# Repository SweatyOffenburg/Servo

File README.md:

# Servo
Publication of Sweaty's servo

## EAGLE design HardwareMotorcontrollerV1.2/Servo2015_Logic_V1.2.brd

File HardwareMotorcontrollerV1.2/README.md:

# Servo
Publication of Sweaty's servo Hardware describede 12th Workshop on Humanoid Soccer Robots IEEE RAS International Conference on Humanoid Robots — November 15-17, 2017, Birmingham (UK)
  /

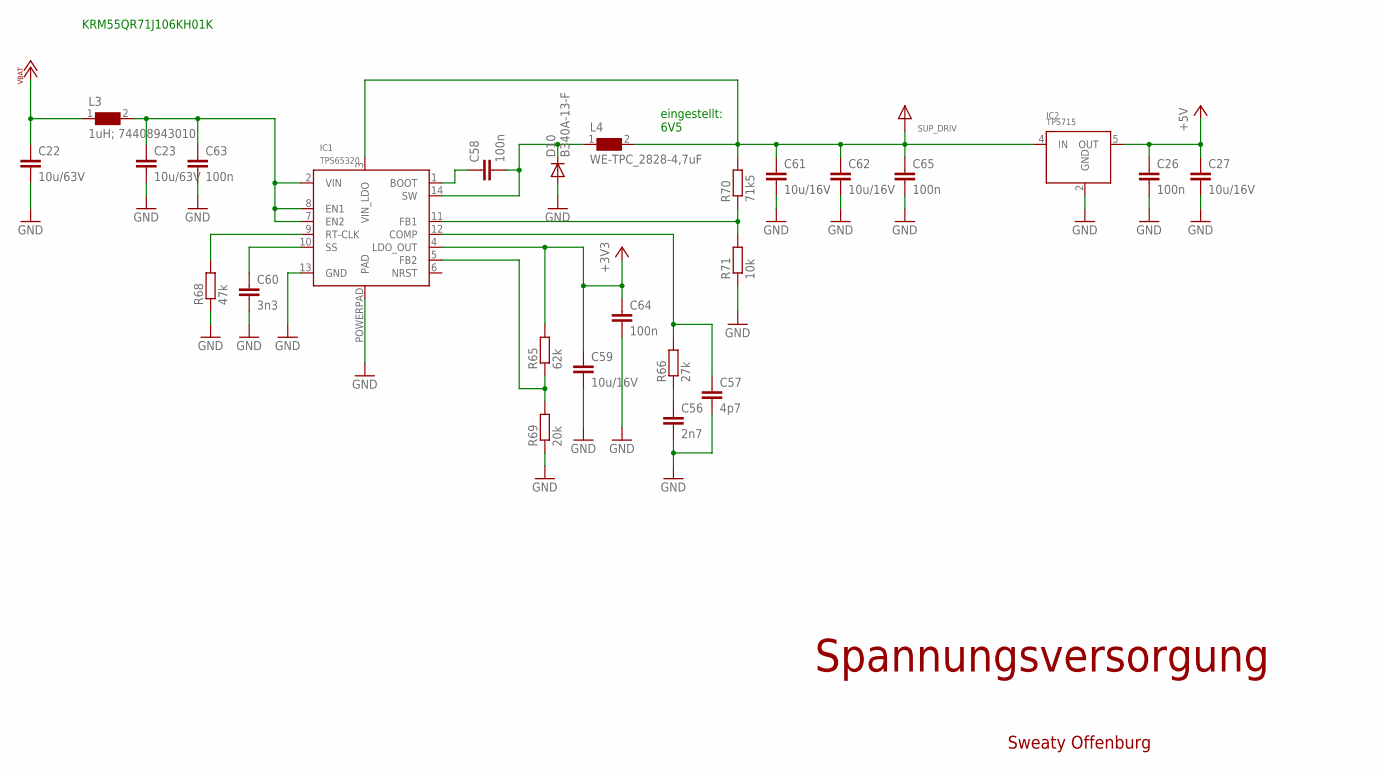
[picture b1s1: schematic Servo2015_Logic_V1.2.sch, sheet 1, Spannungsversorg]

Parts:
C22, C23: 10u/63V; C2220K
C26, C58, C63, C64, C65: 100n; C0603
C27, C59, C61, C62: 10u/16V; C0805
C56: 2n7; C0603
C57: 4p7; C0603
C60: 3n3; C0603
D10: B340A-13-F; SMA
IC1: TPS65320; R.PDSO.G14_PWP
IC2: TPS715; SC-70_DCK_R_PDSO_G5
L3: 1uH; 74408943010; WE-SPC_48XX
L4: WE-TPC_2828-4,7uF; WE-TPC_2828
R65: 62k; R0603
R66: 27k; R0603
R68: 47k; R0603
R69: 20k; R0603
R70: 71k5; R0603
R71: 10k; R0603

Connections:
+3V3: C59.1, C64.1, IC1.4 (LDO_OUT), R65.2; also elsewhere on the board
+5V: C26.1, C27.1, IC2.5 (OUT); also elsewhere on the board
GND: C22.2, C23.2, C26.2, C27.2, C56.2, C57.2, C59.2, C60.2, C61.2, C62.2, C63.2, C64.2, C65.2, D10.A, IC1.13 (GND), IC1.POWERPAD (PAD), IC2.2 (GND), R68.1, R69.1, R71.1; also elsewhere on the board
unnamed: C57.1, IC1.12 (COMP), R66.2
unnamed: C56.1, R66.1
unnamed: IC1.5 (FB2), R65.1, R69.2
unnamed: C58.2, D10.C, IC1.14 (SW), L4.1
unnamed: IC1.11 (FB1), R70.1, R71.2
unnamed: C60.1, IC1.10 (SS)
unnamed: IC1.9 (RT-CLK), R68.2
unnamed: C23.1, C63.1, IC1.2 (VIN), IC1.7 (EN2), IC1.8 (EN1), L3.2
unnamed: C58.1, IC1.1 (BOOT)
SUP_DRIV: C61.1, C62.1, C65.1, IC1.3 (VIN_LDO), IC2.4 (IN), L4.2, R70.2; also elsewhere on the board
VBAT+: C22.1, L3.1; also elsewhere on the board

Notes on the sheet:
Spannungsversorgung
eingestellt: 6V5
KRM55QR71J106KH01K
Sweaty Offenburg

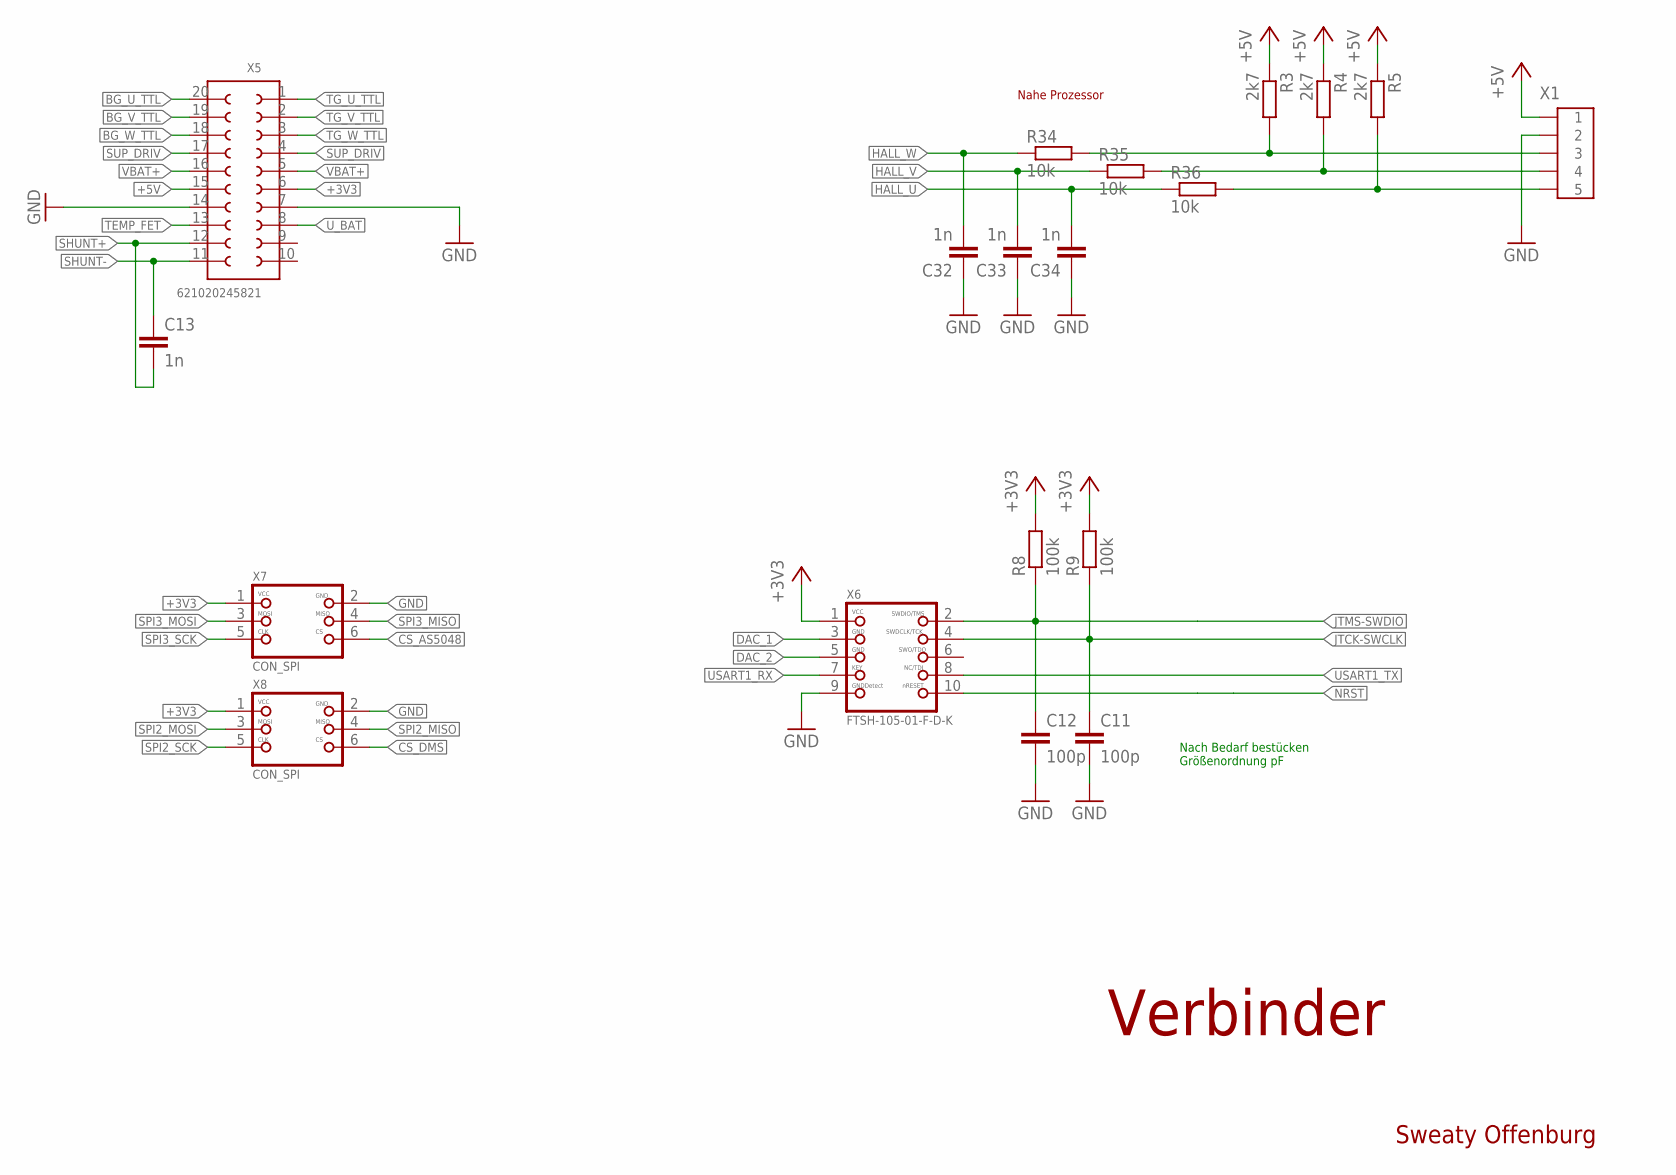
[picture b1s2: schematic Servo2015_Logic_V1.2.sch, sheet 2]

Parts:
C11, C12: 100p; C0603
C13, C32, C33, C34: 1n; C0603
R3, R4, R5: 2k7; R0603
R8, R9: 100k; R0603
R34, R35, R36: 10k; R0603
X1: HALL-5POL-SERVOBOARD; MOLEX-SPOX-5POL-VERT
X5: 621020245821
X6: FTSH-105-01-F-D-K; 2X05_1.27MM_SMT
X7, X8: CON_SPI; 2X03_1.27MM_SMT

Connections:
+3V3: R8.2, R9.2, X5.6, X6.1, X7.1, X8.1; also elsewhere on the board
+5V: R3.1, R4.1, R5.1, X1.1, X5.15; also elsewhere on the board
BG_U_TTL: X5.20; also elsewhere on the board
BG_V_TTL: X5.19; also elsewhere on the board
BG_W_TTL: X5.18; also elsewhere on the board
CS_AS5048: X7.6; also elsewhere on the board
CS_DMS: X8.6; also elsewhere on the board
DAC_1: X6.3; also elsewhere on the board
DAC_2: X6.5; also elsewhere on the board
GND: C11.2, C12.2, C32.1, C33.1, C34.1, X1.2, X5.7, X5.14, X6.9, X7.2, X8.2; also elsewhere on the board
HALL_U: C34.2, R36.1; also elsewhere on the board
HALL_V: C33.2, R35.1; also elsewhere on the board
HALL_W: C32.2, R34.1; also elsewhere on the board
JTCK-SWCLK: C11.1, R9.1, X6.4; also elsewhere on the board
JTMS-SWDIO: C12.1, R8.1, X6.2; also elsewhere on the board
unnamed: R3.2, R34.2, X1.3
unnamed: R4.2, R35.2, X1.4
unnamed: R5.2, R36.2, X1.5
NRST: X6.10; also elsewhere on the board
SHUNT+: C13.2, X5.12; also elsewhere on the board
SHUNT-: C13.1, X5.11; also elsewhere on the board
SPI2_MISO: X8.4; also elsewhere on the board
SPI2_MOSI: X8.3; also elsewhere on the board
SPI2_SCK: X8.5; also elsewhere on the board
SPI3_MISO: X7.4; also elsewhere on the board
SPI3_MOSI: X7.3; also elsewhere on the board
SPI3_SCK: X7.5; also elsewhere on the board
SUP_DRIV: X5.4, X5.17; also elsewhere on the board
TEMP_FET: X5.13; also elsewhere on the board
TG_U_TTL: X5.1; also elsewhere on the board
TG_V_TTL: X5.2; also elsewhere on the board
TG_W_TTL: X5.3; also elsewhere on the board
USART1_RX: X6.7; also elsewhere on the board
USART1_TX: X6.8; also elsewhere on the board
U_BAT: X5.8; also elsewhere on the board
VBAT+: X5.5, X5.16; also elsewhere on the board

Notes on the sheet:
Verbinder
Nahe Prozessor
Nach Bedarf bestücken Größenordnung pF
Sweaty Offenburg

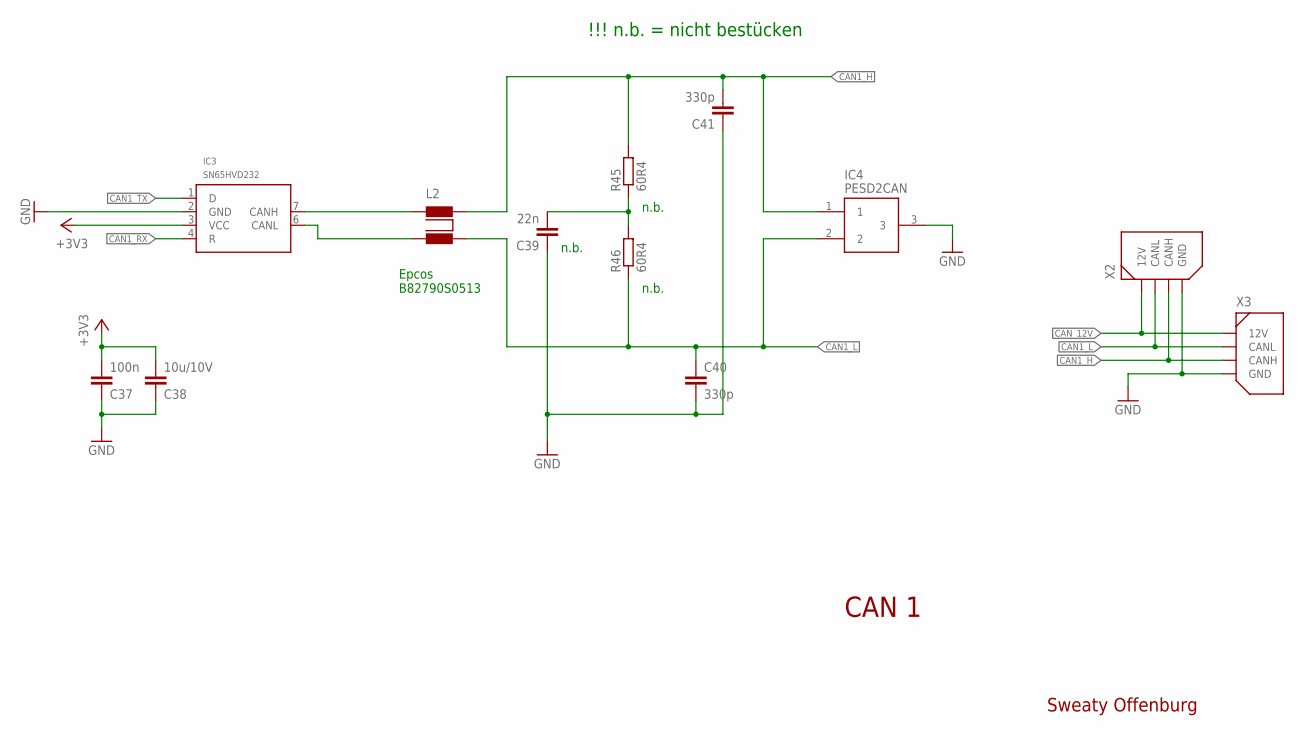
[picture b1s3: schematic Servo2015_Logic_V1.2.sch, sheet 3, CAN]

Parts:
C37: 100n; C0603
C38: 10u/10V; C0603
C39: 22n; C0603
C40, C41: 330p; C0603
IC3: SN65HVD232; SO-8
IC4: PESD2CAN; SOT-23(TO263AB)
L2: B82790S0513; B82790C0/S0
R45, R46: 60R4; R0805
X2, X3: CAN-4POL; MOLEX-SPOX-4PO

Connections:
+3V3: C37.2, C38.2, IC3.3 (VCC); also elsewhere on the board
CAN1_H: C41.2, IC4.1, L2.2, R45.2, X2.P$3 (CANH), X3.P$3 (CANH)
CAN1_L: C40.1, IC4.2, L2.3, R46.1, X2.P$2 (CANL), X3.P$2 (CANL)
CAN1_RX: IC3.4 (R); also elsewhere on the board
CAN1_TX: IC3.1 (D); also elsewhere on the board
CAN_12V: X2.P$1 (12V), X3.P$1 (12V)
GND: C37.1, C38.1, C39.1, C40.2, C41.1, IC3.2 (GND), IC4.3, X2.P$4 (GND), X3.P$4 (GND); also elsewhere on the board
unnamed: C39.2, R45.1, R46.2
unnamed: IC3.7 (CANH), L2.1
unnamed: IC3.6 (CANL), L2.4

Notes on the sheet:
Epcos B82790S0513
CAN 1
n.b.
!!! n.b. = nicht bestücken
Sweaty Offenburg

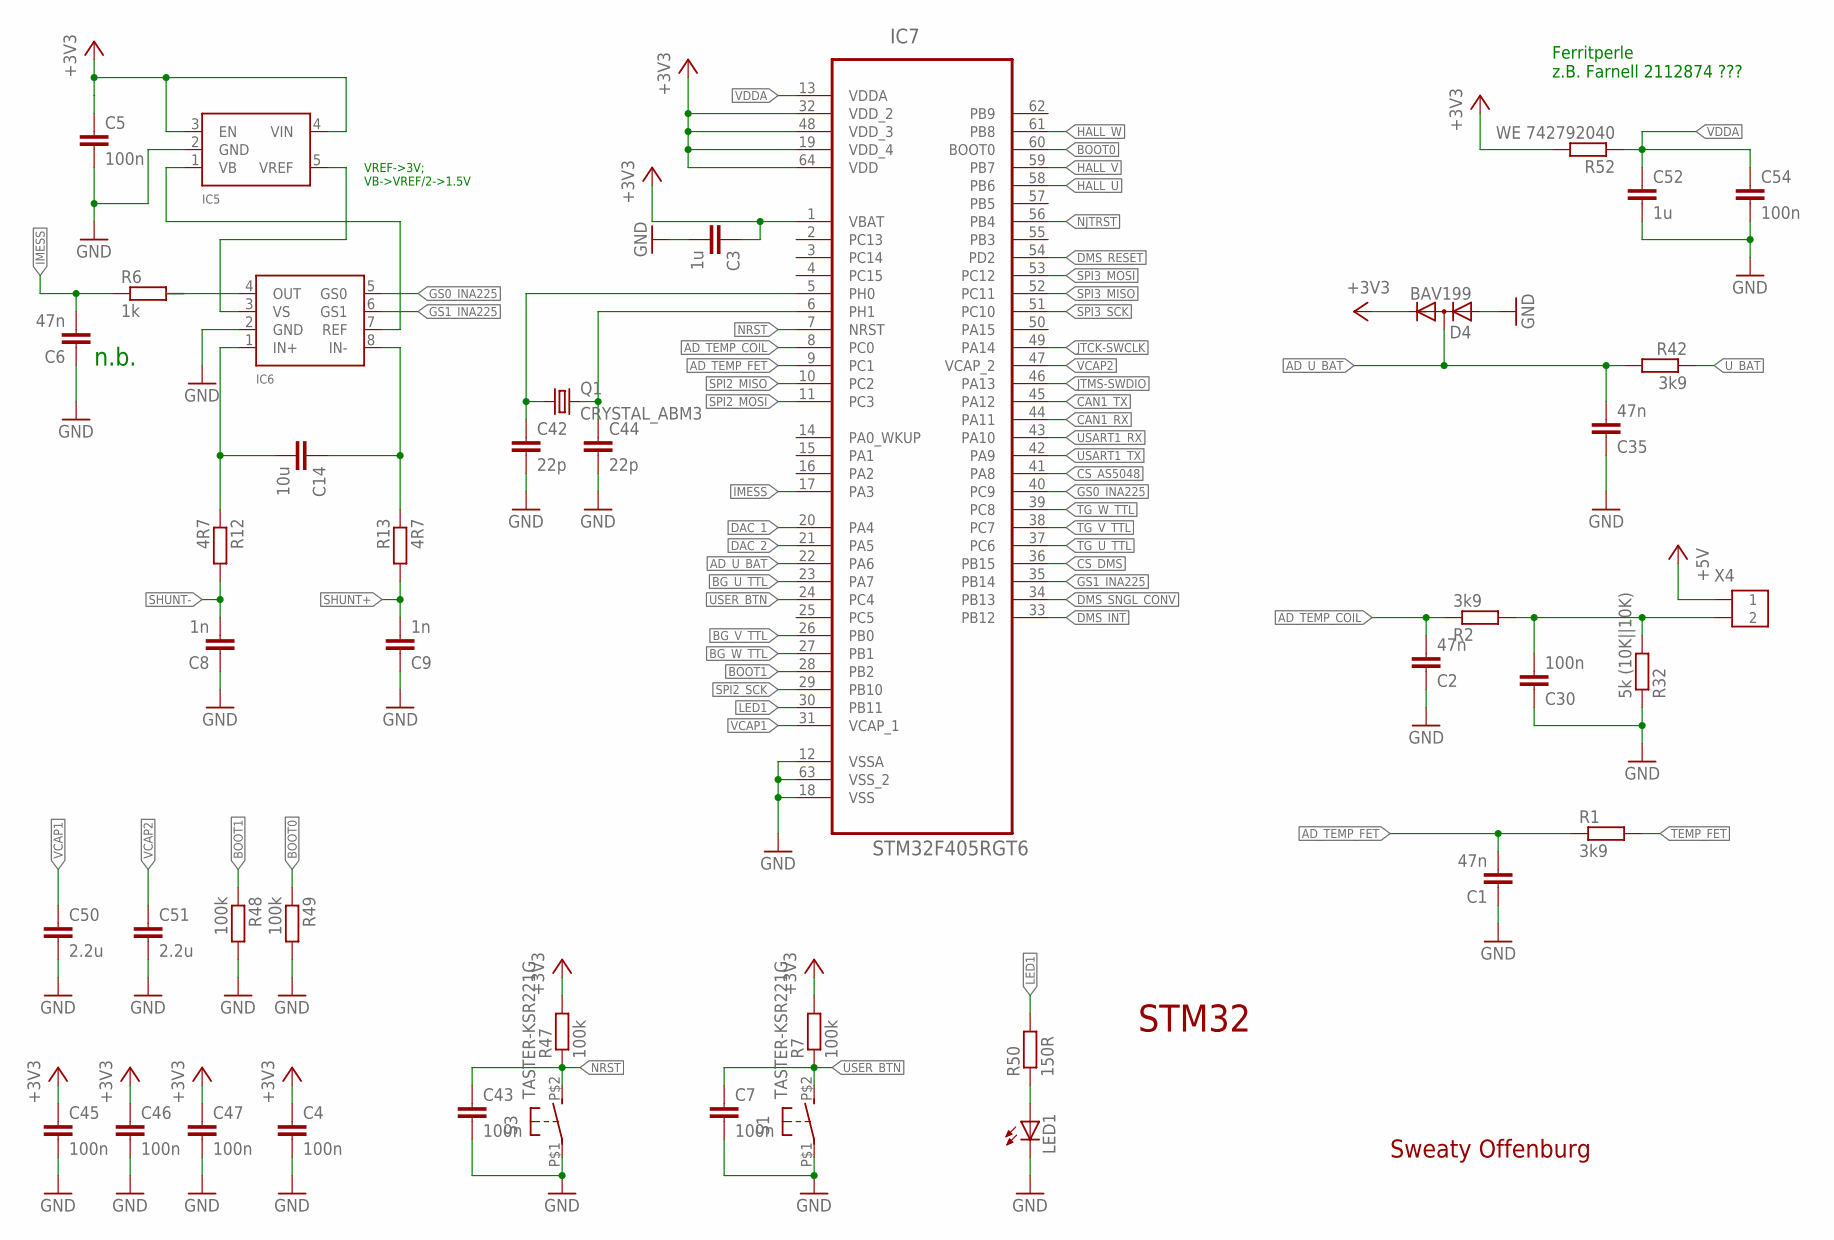
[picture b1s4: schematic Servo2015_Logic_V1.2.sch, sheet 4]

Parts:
C1, C2, C6, C35: 47n; C0603
C3, C52: 1u; C0603
C4, C5, C7, C30, C43, C45, C46, C47, C54: 100n; C0603
C8, C9: 1n; C0603
C14: 10u; C0603
C42, C44: 22p; C0603
C50, C51: 2.2u; C0603
D4: BAV199; SOT23
IC5: REF2030; R-PDSO-G5
IC6: INA225; S-PDSO-G8
IC7: STM32F405RGT6; QFP50P1200X1200X160-64N
LED1: LEDCHIPLED_0805; CHIPLED_0805
Q1: CRYSTAL_ABM3; CRYSTAL-5X3.2
R1, R2, R42: 3k9; R0603
R6: 1k; R0603
R7, R47, R48, R49: 100k; R0603
R12, R13: 4R7; R0603
R32: 5k (10K||10K); R0603
R50: 150R; R0603
R52: WE 742792040; R0805
S1, S3: TASTER-KSR221G; KSR-TASTER
X4: KRAFTSENSOR-2POL; MOLEX-SPOX-2POL

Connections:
+3V3: C3.1, C4.1, C5.1, C45.1, C46.1, C47.1, D4.2 (C), IC5.3 (EN), IC5.4 (VIN), IC7.1 (VBAT), IC7.19 (VDD_4), IC7.32 (VDD_2), IC7.48 (VDD_3), IC7.64 (VDD), R7.2, R47.2, R52.2; also elsewhere on the board
+5V: X4.P$1 (1); also elsewhere on the board
AD_TEMP_COIL: C2.2, IC7.8 (PC0), R2.1
AD_TEMP_FET: C1.2, IC7.9 (PC1), R1.1
AD_U_BAT: C35.2, D4.3 (AC), IC7.22 (PA6), R42.2
BG_U_TTL: IC7.23 (PA7); also elsewhere on the board
BG_V_TTL: IC7.26 (PB0); also elsewhere on the board
BG_W_TTL: IC7.27 (PB1); also elsewhere on the board
BOOT0: IC7.60 (BOOT0), R49.1
BOOT1: IC7.28 (PB2), R48.1
CAN1_RX: IC7.44 (PA11); also elsewhere on the board
CAN1_TX: IC7.45 (PA12); also elsewhere on the board
CS_AS5048: IC7.41 (PA8); also elsewhere on the board
CS_DMS: IC7.36 (PB15); also elsewhere on the board
DAC_1: IC7.20 (PA4); also elsewhere on the board
DAC_2: IC7.21 (PA5); also elsewhere on the board
DMS_INT: IC7.33 (PB12)
DMS_RESET: IC7.54 (PD2)
DMS_SNGL_CONV: IC7.34 (PB13)
GND: C1.1, C2.1, C3.2, C4.2, C5.2, C6.1, C7.2, C8.1, C9.1, C30.1, C35.1, C42.2, C43.2, C44.2, C45.2, C46.2, C47.2, C50.2, C51.2, C52.2, C54.2, D4.1 (A), IC5.2 (GND), IC6.2 (GND), IC7.12 (VSSA), IC7.18 (VSS), IC7.63 (VSS_2), LED1.C, R32.1, R48.2, R49.2, S1.P$1, S3.P$1; also elsewhere on the board
GS0_INA225: IC6.5 (GS0), IC7.40 (PC9)
GS1_INA225: IC6.6 (GS1), IC7.35 (PB14)
HALL_U: IC7.58 (PB6); also elsewhere on the board
HALL_V: IC7.59 (PB7); also elsewhere on the board
HALL_W: IC7.61 (PB8); also elsewhere on the board
IC6: C14.2, IC6.1 (IN+), R12.1
IMESS: C6.2, IC7.17 (PA3), R6.1
JTCK-SWCLK: IC7.49 (PA14); also elsewhere on the board
JTMS-SWDIO: IC7.46 (PA13); also elsewhere on the board
LED1: IC7.30 (PB11), R50.2
unnamed: C14.1, IC6.8 (IN-), R13.1
unnamed: LED1.A, R50.1
unnamed: IC6.4 (OUT), R6.2
unnamed: IC5.5 (VREF), IC6.3 (VS)
unnamed: IC5.1 (VB), IC6.7 (REF)
unnamed: C44.1, IC7.6 (PH1), Q1.P$2 (2)
unnamed: C42.1, IC7.5 (PH0), Q1.P$1 (1)
NJTRST: IC7.56 (PB4)
NRST: C43.1, IC7.7 (NRST), R47.1, S3.P$2 (S); also elsewhere on the board
SHUNT+: C9.2, R13.2; also elsewhere on the board
SHUNT-: C8.2, R12.2; also elsewhere on the board
SPI2_MISO: IC7.10 (PC2); also elsewhere on the board
SPI2_MOSI: IC7.11 (PC3); also elsewhere on the board
SPI2_SCK: IC7.29 (PB10); also elsewhere on the board
SPI3_MISO: IC7.52 (PC11); also elsewhere on the board
SPI3_MOSI: IC7.53 (PC12); also elsewhere on the board
SPI3_SCK: IC7.51 (PC10); also elsewhere on the board
TEMP_COIL: C30.2, R2.2, R32.2, X4.P$2 (2)
TEMP_FET: R1.2; also elsewhere on the board
TG_U_TTL: IC7.37 (PC6); also elsewhere on the board
TG_V_TTL: IC7.38 (PC7); also elsewhere on the board
TG_W_TTL: IC7.39 (PC8); also elsewhere on the board
USART1_RX: IC7.43 (PA10); also elsewhere on the board
USART1_TX: IC7.42 (PA9); also elsewhere on the board
USER_BTN: C7.1, IC7.24 (PC4), R7.1, S1.P$2 (S)
U_BAT: R42.1; also elsewhere on the board
VCAP1: C50.1, IC7.31 (VCAP_1)
VCAP2: C51.1, IC7.47 (VCAP_2)
VDDA: C52.1, C54.1, IC7.13 (VDDA), R52.1

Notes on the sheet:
Ferritperle z.B. Farnell 2112874 ???
STM32
VREF->3V; VB->VREF/2->1.5V
n.b.
Sweaty Offenburg

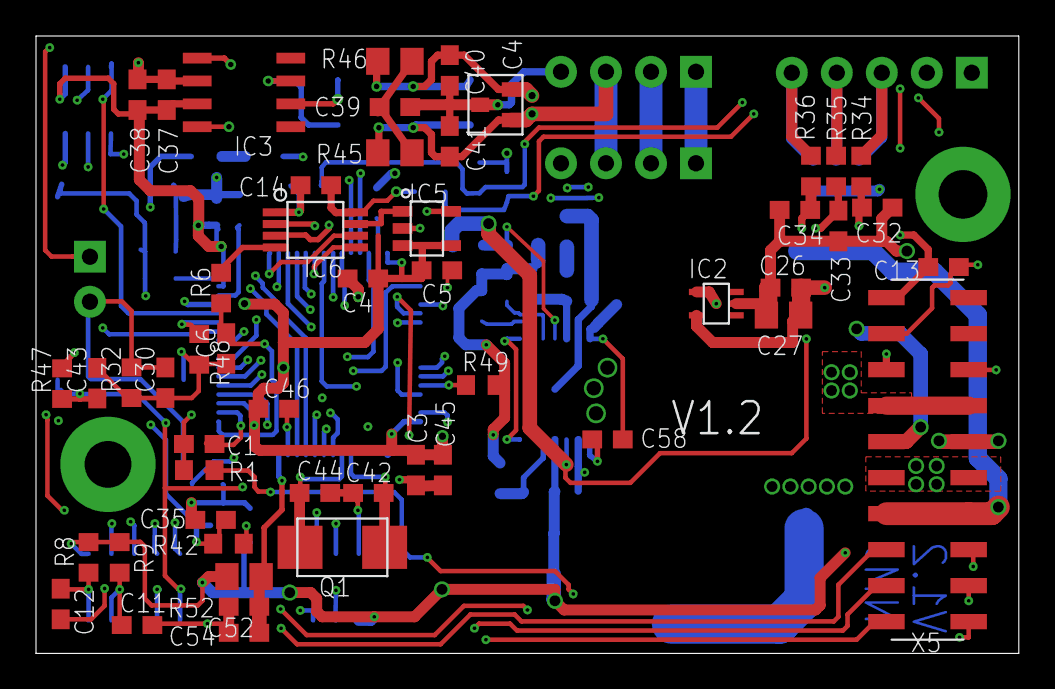
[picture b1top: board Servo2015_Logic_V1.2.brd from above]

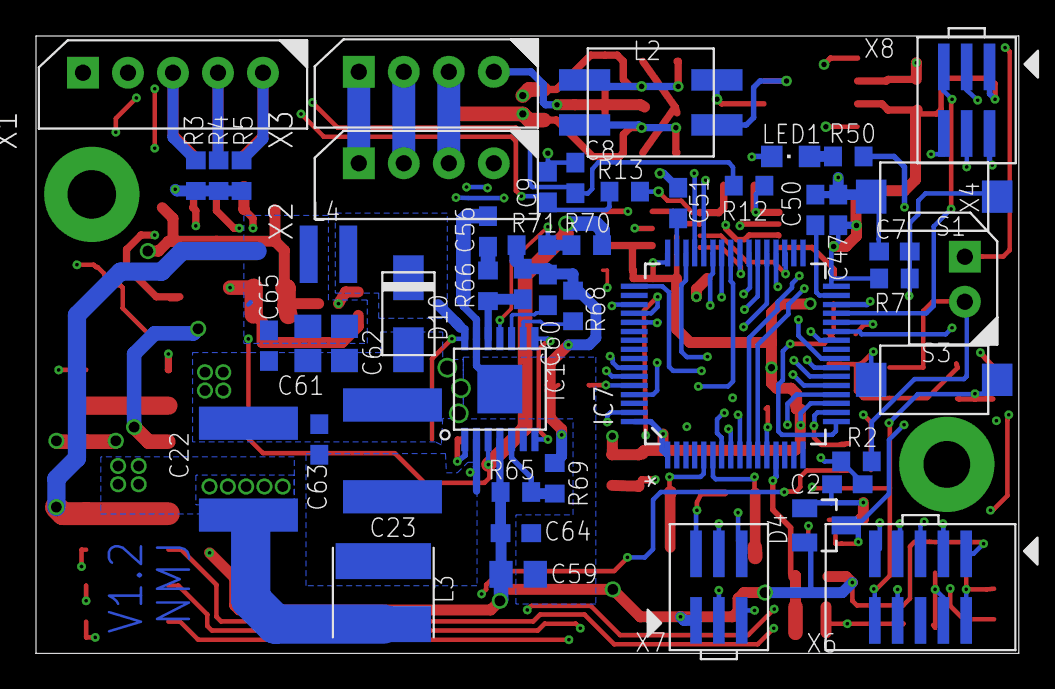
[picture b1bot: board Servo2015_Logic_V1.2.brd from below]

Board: 4 copper layers, 54.6 x 34.3 mm, 101 parts (49 on the bottom side), 75 nets.

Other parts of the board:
U$1: A4L-LOC

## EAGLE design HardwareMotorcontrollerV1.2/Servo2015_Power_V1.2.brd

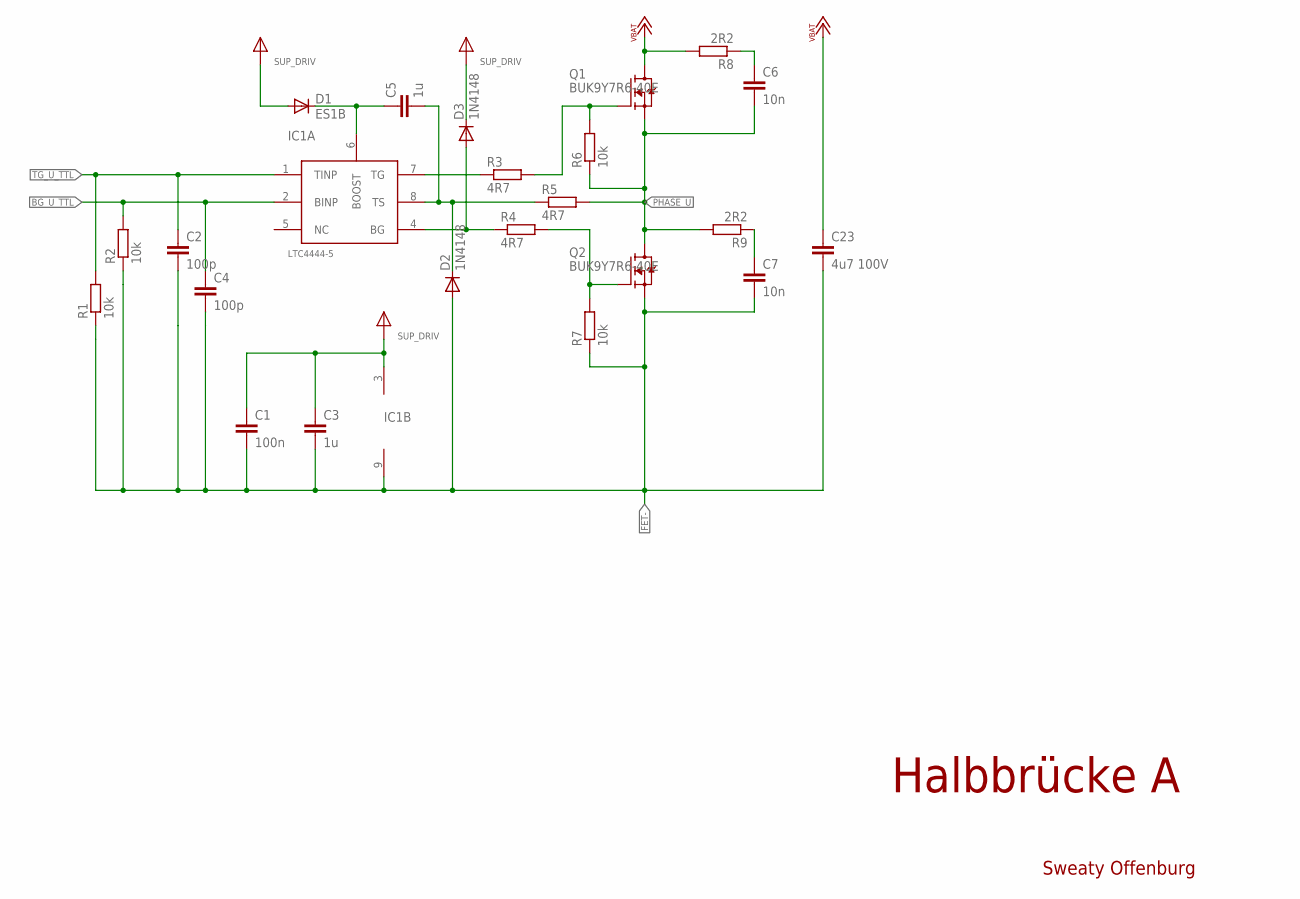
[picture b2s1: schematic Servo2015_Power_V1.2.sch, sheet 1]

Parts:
C1: 100n; C0603
C2, C4: 100p; C0603
C3, C5: 1u; C0603
C6, C7: 10n; C1210
C23: 4u7 100V; C2220K
D1: ES1B; DO214AC
D2, D3: 1N4148; SOD123
IC1: LTC4444-5; MS8E
Q1, Q2: BUK9Y7R6-40E; LFPAK56
R1, R2, R6, R7: 10k; R0603
R3, R4, R5: 4R7; R0805
R8, R9: 2R2; R1206

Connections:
BGR_A: Q2.4 (G), R4.2, R7.2
BG_U_TTL: C4.1, IC1.2 (BINP), R2.2; also elsewhere on the board
FET-: C1.2, C2.2, C3.2, C4.2, C7.2, C23.2, D2.A, IC1.9 (GND), Q2.1 (S), Q2.2 (S), Q2.3 (S), R1.1, R2.1, R7.1; also elsewhere on the board
unnamed: IC1.7 (TG), R3.1
unnamed: C5.2, D2.C, IC1.8 (TS), R5.1
unnamed: D3.A, IC1.4 (BG), R4.1
unnamed: C5.1, D1.C, IC1.6 (BOOST)
unnamed: C6.1, R8.1
unnamed: C7.1, R9.1
PHASE_U: C6.2, Q1.1 (S), Q1.2 (S), Q1.3 (S), Q2.5-8 (D), R5.2, R6.1, R9.2; also elsewhere on the board
SUP_DRIV: C1.1, C3.1, D1.A, D3.C, IC1.3 (VCC); also elsewhere on the board
TGR_A: Q1.4 (G), R3.2, R6.2
TG_U_TTL: C2.1, IC1.1 (TINP), R1.2; also elsewhere on the board
VBAT+: C23.1, Q1.5-8 (D), R8.2; also elsewhere on the board

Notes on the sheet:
Halbbrücke A
Sweaty Offenburg

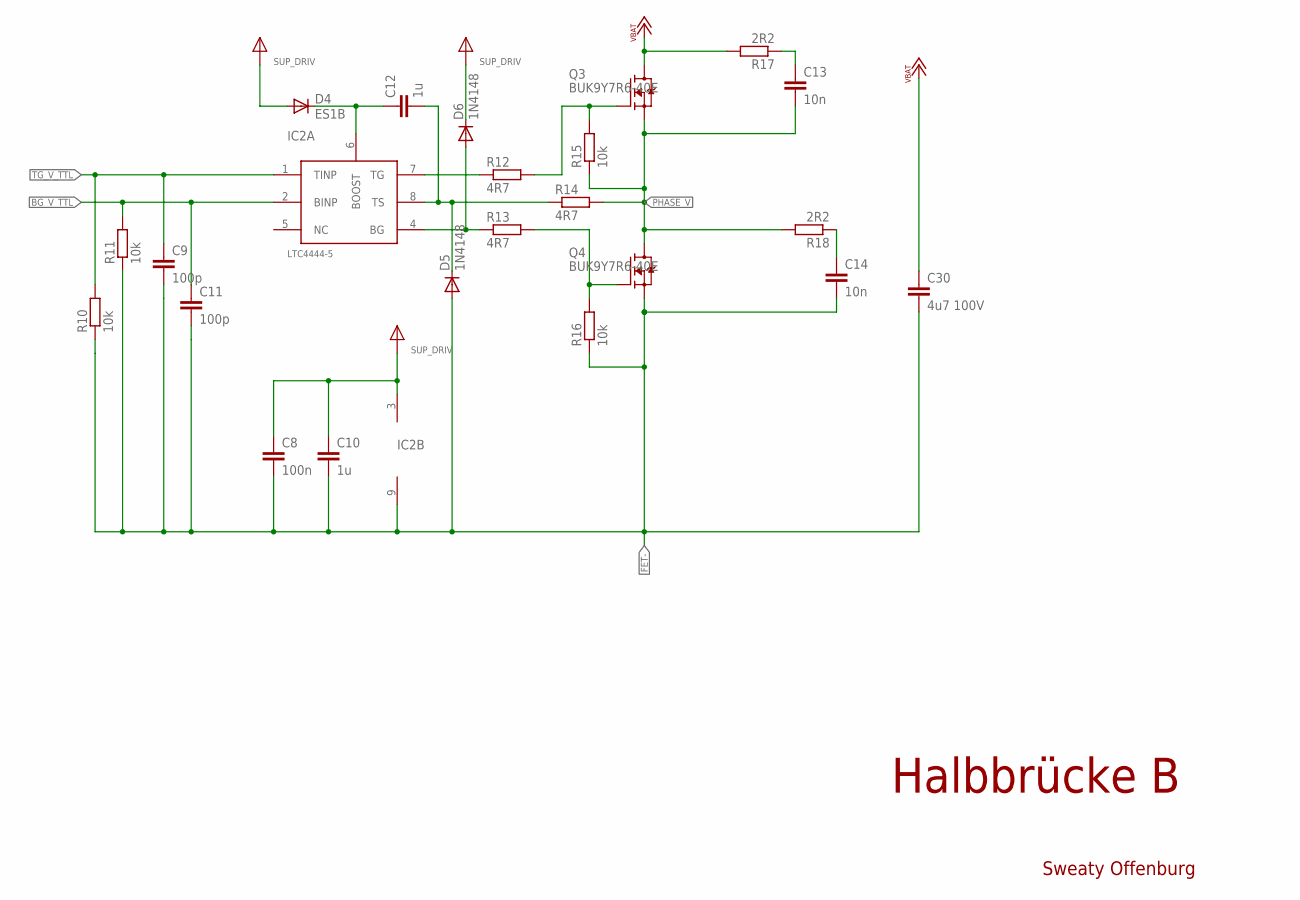
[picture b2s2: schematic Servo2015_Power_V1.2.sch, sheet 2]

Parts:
C8: 100n; C0603
C9, C11: 100p; C0603
C10, C12: 1u; C0603
C13, C14: 10n; C1210
C30: 4u7 100V; C2220K
D4: ES1B; DO214AC
D5, D6: 1N4148; SOD123
IC2: LTC4444-5; MS8E
Q3, Q4: BUK9Y7R6-40E; LFPAK56
R10, R11, R15, R16: 10k; R0603
R12, R13, R14: 4R7; R0805
R17, R18: 2R2; R1206

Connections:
BGR_B: Q4.4 (G), R13.2, R16.2
BG_V_TTL: C11.1, IC2.2 (BINP), R11.2; also elsewhere on the board
FET-: C8.2, C9.2, C10.2, C11.2, C14.2, C30.2, D5.A, IC2.9 (GND), Q4.1 (S), Q4.2 (S), Q4.3 (S), R10.1, R11.1, R16.1; also elsewhere on the board
unnamed: IC2.7 (TG), R12.1
unnamed: C12.2, D5.C, IC2.8 (TS), R14.1
unnamed: D6.A, IC2.4 (BG), R13.1
unnamed: C12.1, D4.C, IC2.6 (BOOST)
unnamed: C13.1, R17.1
unnamed: C14.1, R18.1
PHASE_V: C13.2, Q3.1 (S), Q3.2 (S), Q3.3 (S), Q4.5-8 (D), R14.2, R15.1, R18.2; also elsewhere on the board
SUP_DRIV: C8.1, C10.1, D4.A, D6.C, IC2.3 (VCC); also elsewhere on the board
TGR_B: Q3.4 (G), R12.2, R15.2
TG_V_TTL: C9.1, IC2.1 (TINP), R10.2; also elsewhere on the board
VBAT+: C30.1, Q3.5-8 (D), R17.2; also elsewhere on the board

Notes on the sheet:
Halbbrücke B
Sweaty Offenburg

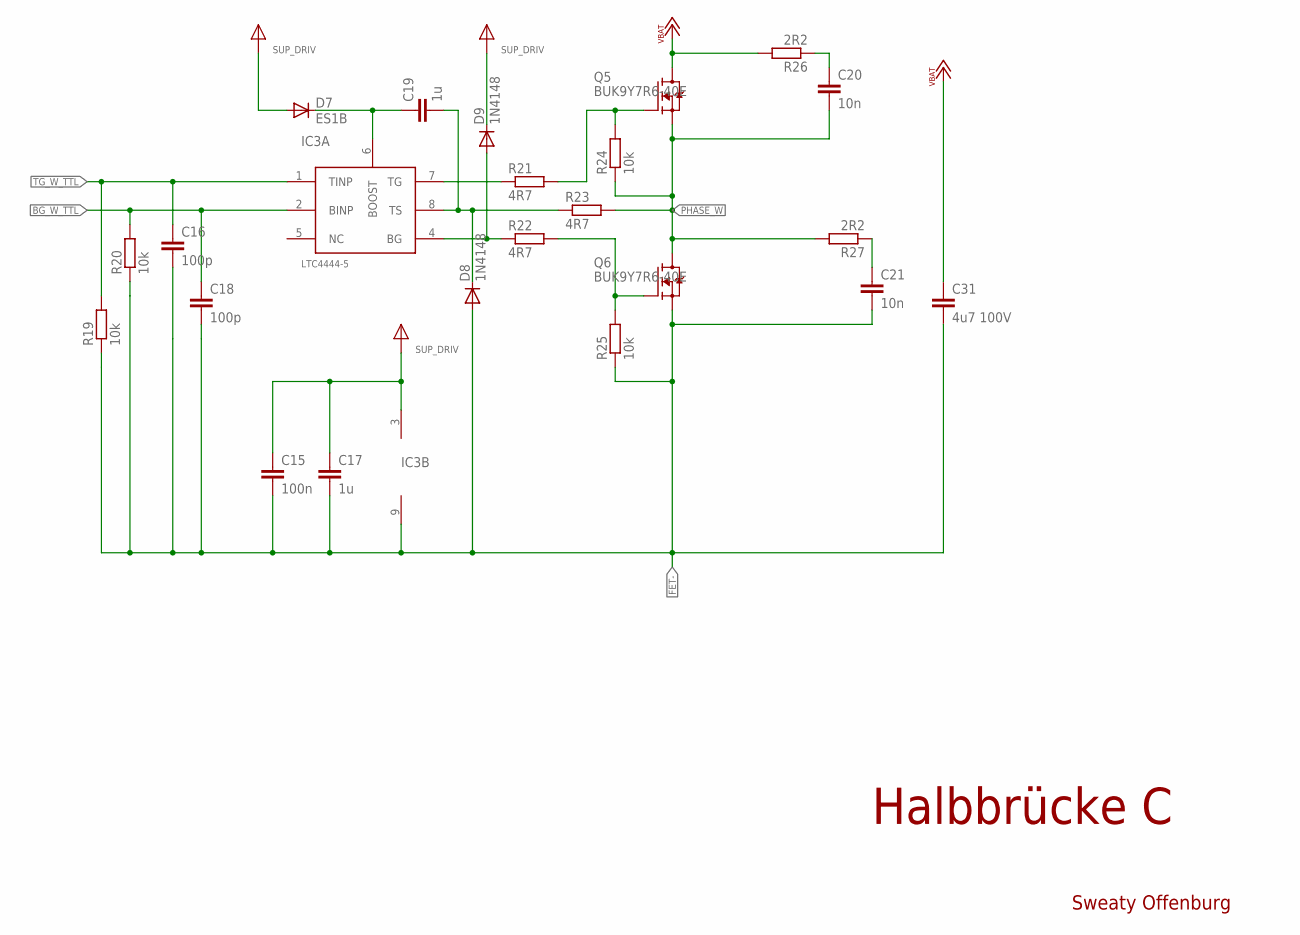
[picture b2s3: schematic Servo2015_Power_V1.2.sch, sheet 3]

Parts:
C15: 100n; C0603
C16, C18: 100p; C0603
C17, C19: 1u; C0603
C20, C21: 10n; C1210
C31: 4u7 100V; C2220K
D7: ES1B; DO214AC
D8, D9: 1N4148; SOD123
IC3: LTC4444-5; MS8E
Q5, Q6: BUK9Y7R6-40E; LFPAK56
R19, R20, R24, R25: 10k; R0603
R21, R22, R23: 4R7; R0805
R26, R27: 2R2; R1206

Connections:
BGR_C: Q6.4 (G), R22.2, R25.2
BG_W_TTL: C18.1, IC3.2 (BINP), R20.2; also elsewhere on the board
FET-: C15.2, C16.2, C17.2, C18.2, C21.2, C31.2, D8.A, IC3.9 (GND), Q6.1 (S), Q6.2 (S), Q6.3 (S), R19.1, R20.1, R25.1; also elsewhere on the board
unnamed: IC3.7 (TG), R21.1
unnamed: C19.2, D8.C, IC3.8 (TS), R23.1
unnamed: D9.A, IC3.4 (BG), R22.1
unnamed: C19.1, D7.C, IC3.6 (BOOST)
unnamed: C20.1, R26.1
unnamed: C21.1, R27.1
PHASE_W: C20.2, Q5.1 (S), Q5.2 (S), Q5.3 (S), Q6.5-8 (D), R23.2, R24.1, R27.2; also elsewhere on the board
SUP_DRIV: C15.1, C17.1, D7.A, D9.C, IC3.3 (VCC); also elsewhere on the board
TGR_C: Q5.4 (G), R21.2, R24.2
TG_W_TTL: C16.1, IC3.1 (TINP), R19.2; also elsewhere on the board
VBAT+: C31.1, Q5.5-8 (D), R26.2; also elsewhere on the board

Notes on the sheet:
Halbbrücke C
Sweaty Offenburg

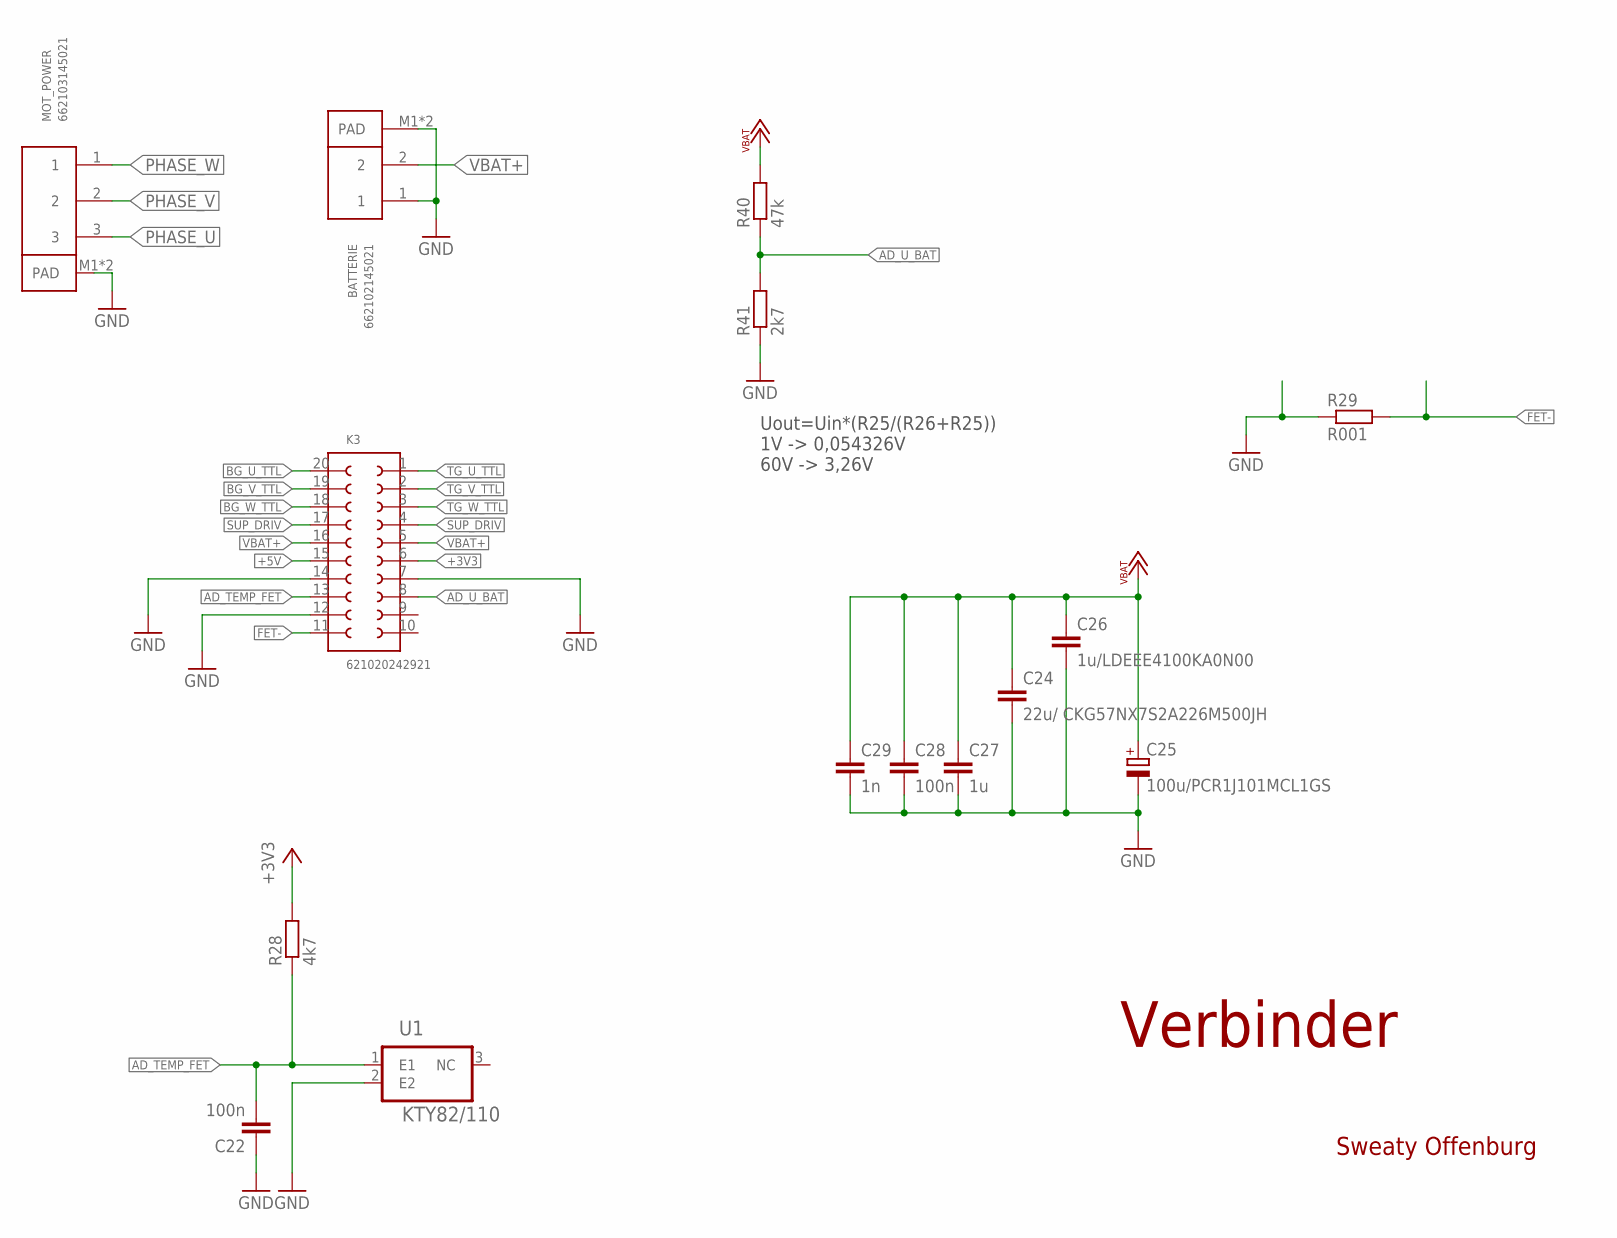
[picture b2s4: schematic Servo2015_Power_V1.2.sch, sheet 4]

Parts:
BATTERIE: 662102145021
C22, C28: 100n; C0603
C24: 22u/ CKG57NX7S2A226M500JH; CKG57-5750-CC2220
C25: 100u/PCR1J101MCL1GS; PANASONIC_G
C26: 1u/LDEEE4100KA0N00; C2824
C27: 1u; C1210
C29: 1n; C0603
K3: 621020242921
MOT_POWER: 662103145021
R28: 4k7; R0603
R29: R001; R2512
R40: 47k; R0603
R41: 2k7; R0603
U1: KTY82/110; SOT95P230X110-3N

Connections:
+3V3: K3.6, R28.2
+5V: K3.15
AD_TEMP_FET: C22.2, K3.13, R28.1, U1.1 (E1)
AD_U_BAT: K3.8, R40.1, R41.2
BG_U_TTL: K3.20; also elsewhere on the board
BG_V_TTL: K3.19; also elsewhere on the board
BG_W_TTL: K3.18; also elsewhere on the board
FET-: K3.11, R29.2; also elsewhere on the board
GND: BATTERIE.1, BATTERIE.M1 (PAD), BATTERIE.M2 (PAD), C22.1, C24.2, C25.-, C26.2, C27.2, C28.2, C29.2, K3.7, K3.12, K3.14, MOT_POWER.M1 (PAD), MOT_POWER.M2 (PAD), R29.1, R41.1, U1.2 (E2)
PHASE_U: MOT_POWER.3; also elsewhere on the board
PHASE_V: MOT_POWER.2; also elsewhere on the board
PHASE_W: MOT_POWER.1; also elsewhere on the board
SUP_DRIV: K3.4, K3.17; also elsewhere on the board
TG_U_TTL: K3.1; also elsewhere on the board
TG_V_TTL: K3.2; also elsewhere on the board
TG_W_TTL: K3.3; also elsewhere on the board
VBAT+: BATTERIE.2, C24.1, C25.+, C26.1, C27.1, C28.1, C29.1, K3.5, K3.16, R40.2; also elsewhere on the board

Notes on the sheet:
Verbinder
Uout=Uin*(R25/(R26+R25)) 1V -> 0,054326V 60V -> 3,26V
Sweaty Offenburg

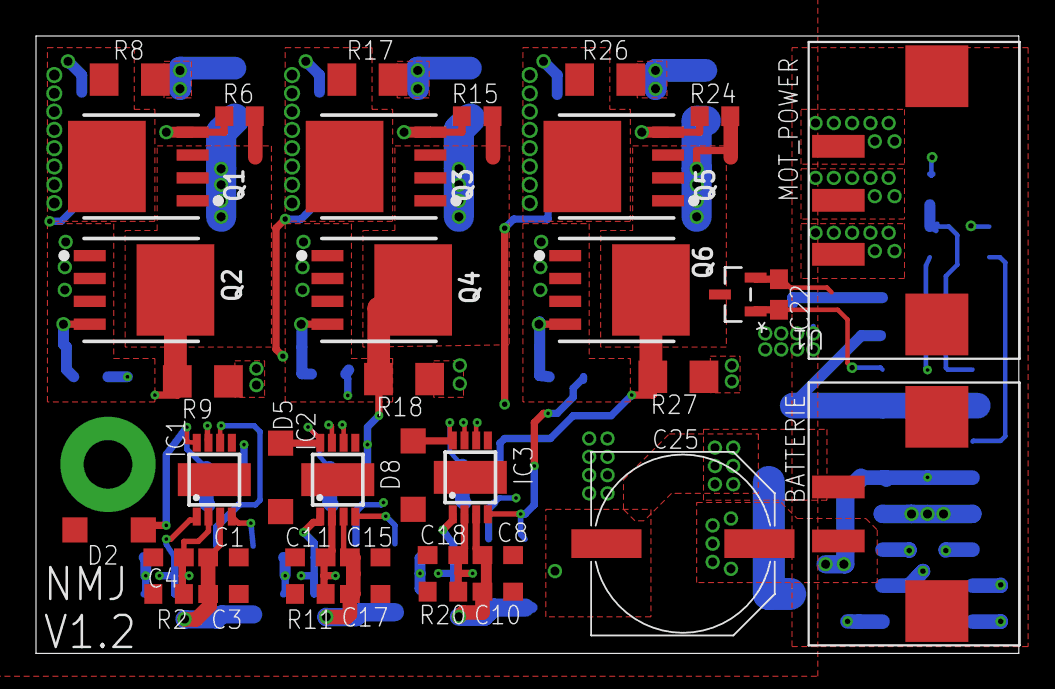
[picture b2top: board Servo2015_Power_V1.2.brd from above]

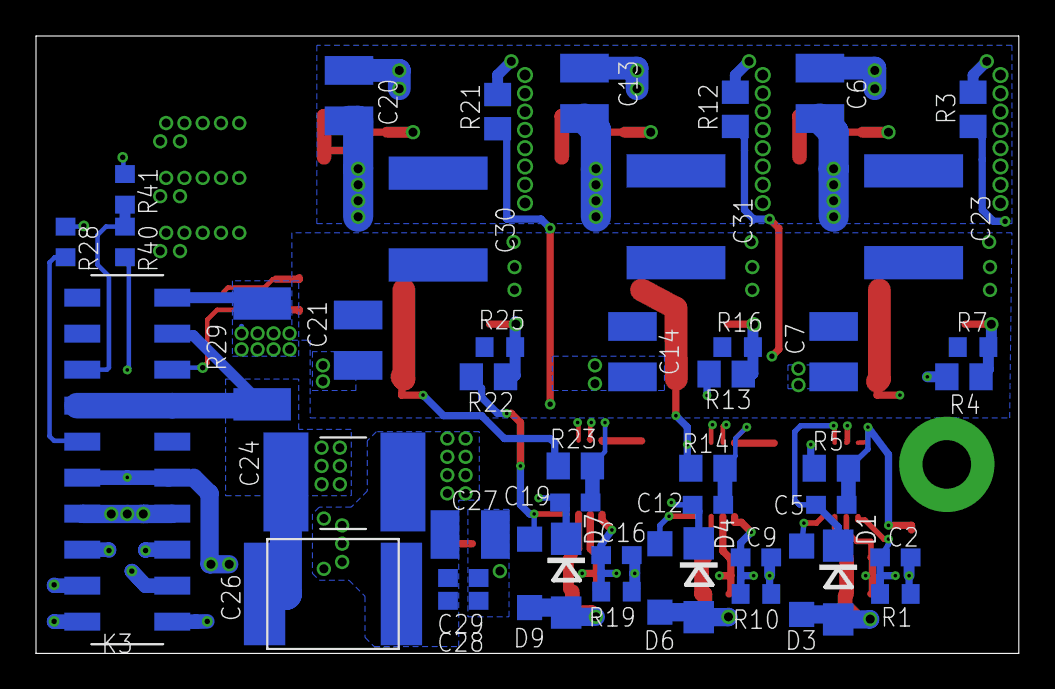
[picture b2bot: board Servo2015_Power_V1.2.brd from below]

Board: 4 copper layers, 54.6 x 34.3 mm, 85 parts (46 on the bottom side), 40 nets.

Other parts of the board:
U$1: A4L-LOC

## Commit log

2017-11-11 Added MIT license
2017-11-11 Sweaty's Motorcontroller

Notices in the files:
parts and their libraries:
microbuilder: This work is placed in the public domain, and may be freely used for commercial and non-commercial work with the following conditions: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
Wurth_Elektronik_Electromechanic_Board_t: Copyright: Würth Elektronik
